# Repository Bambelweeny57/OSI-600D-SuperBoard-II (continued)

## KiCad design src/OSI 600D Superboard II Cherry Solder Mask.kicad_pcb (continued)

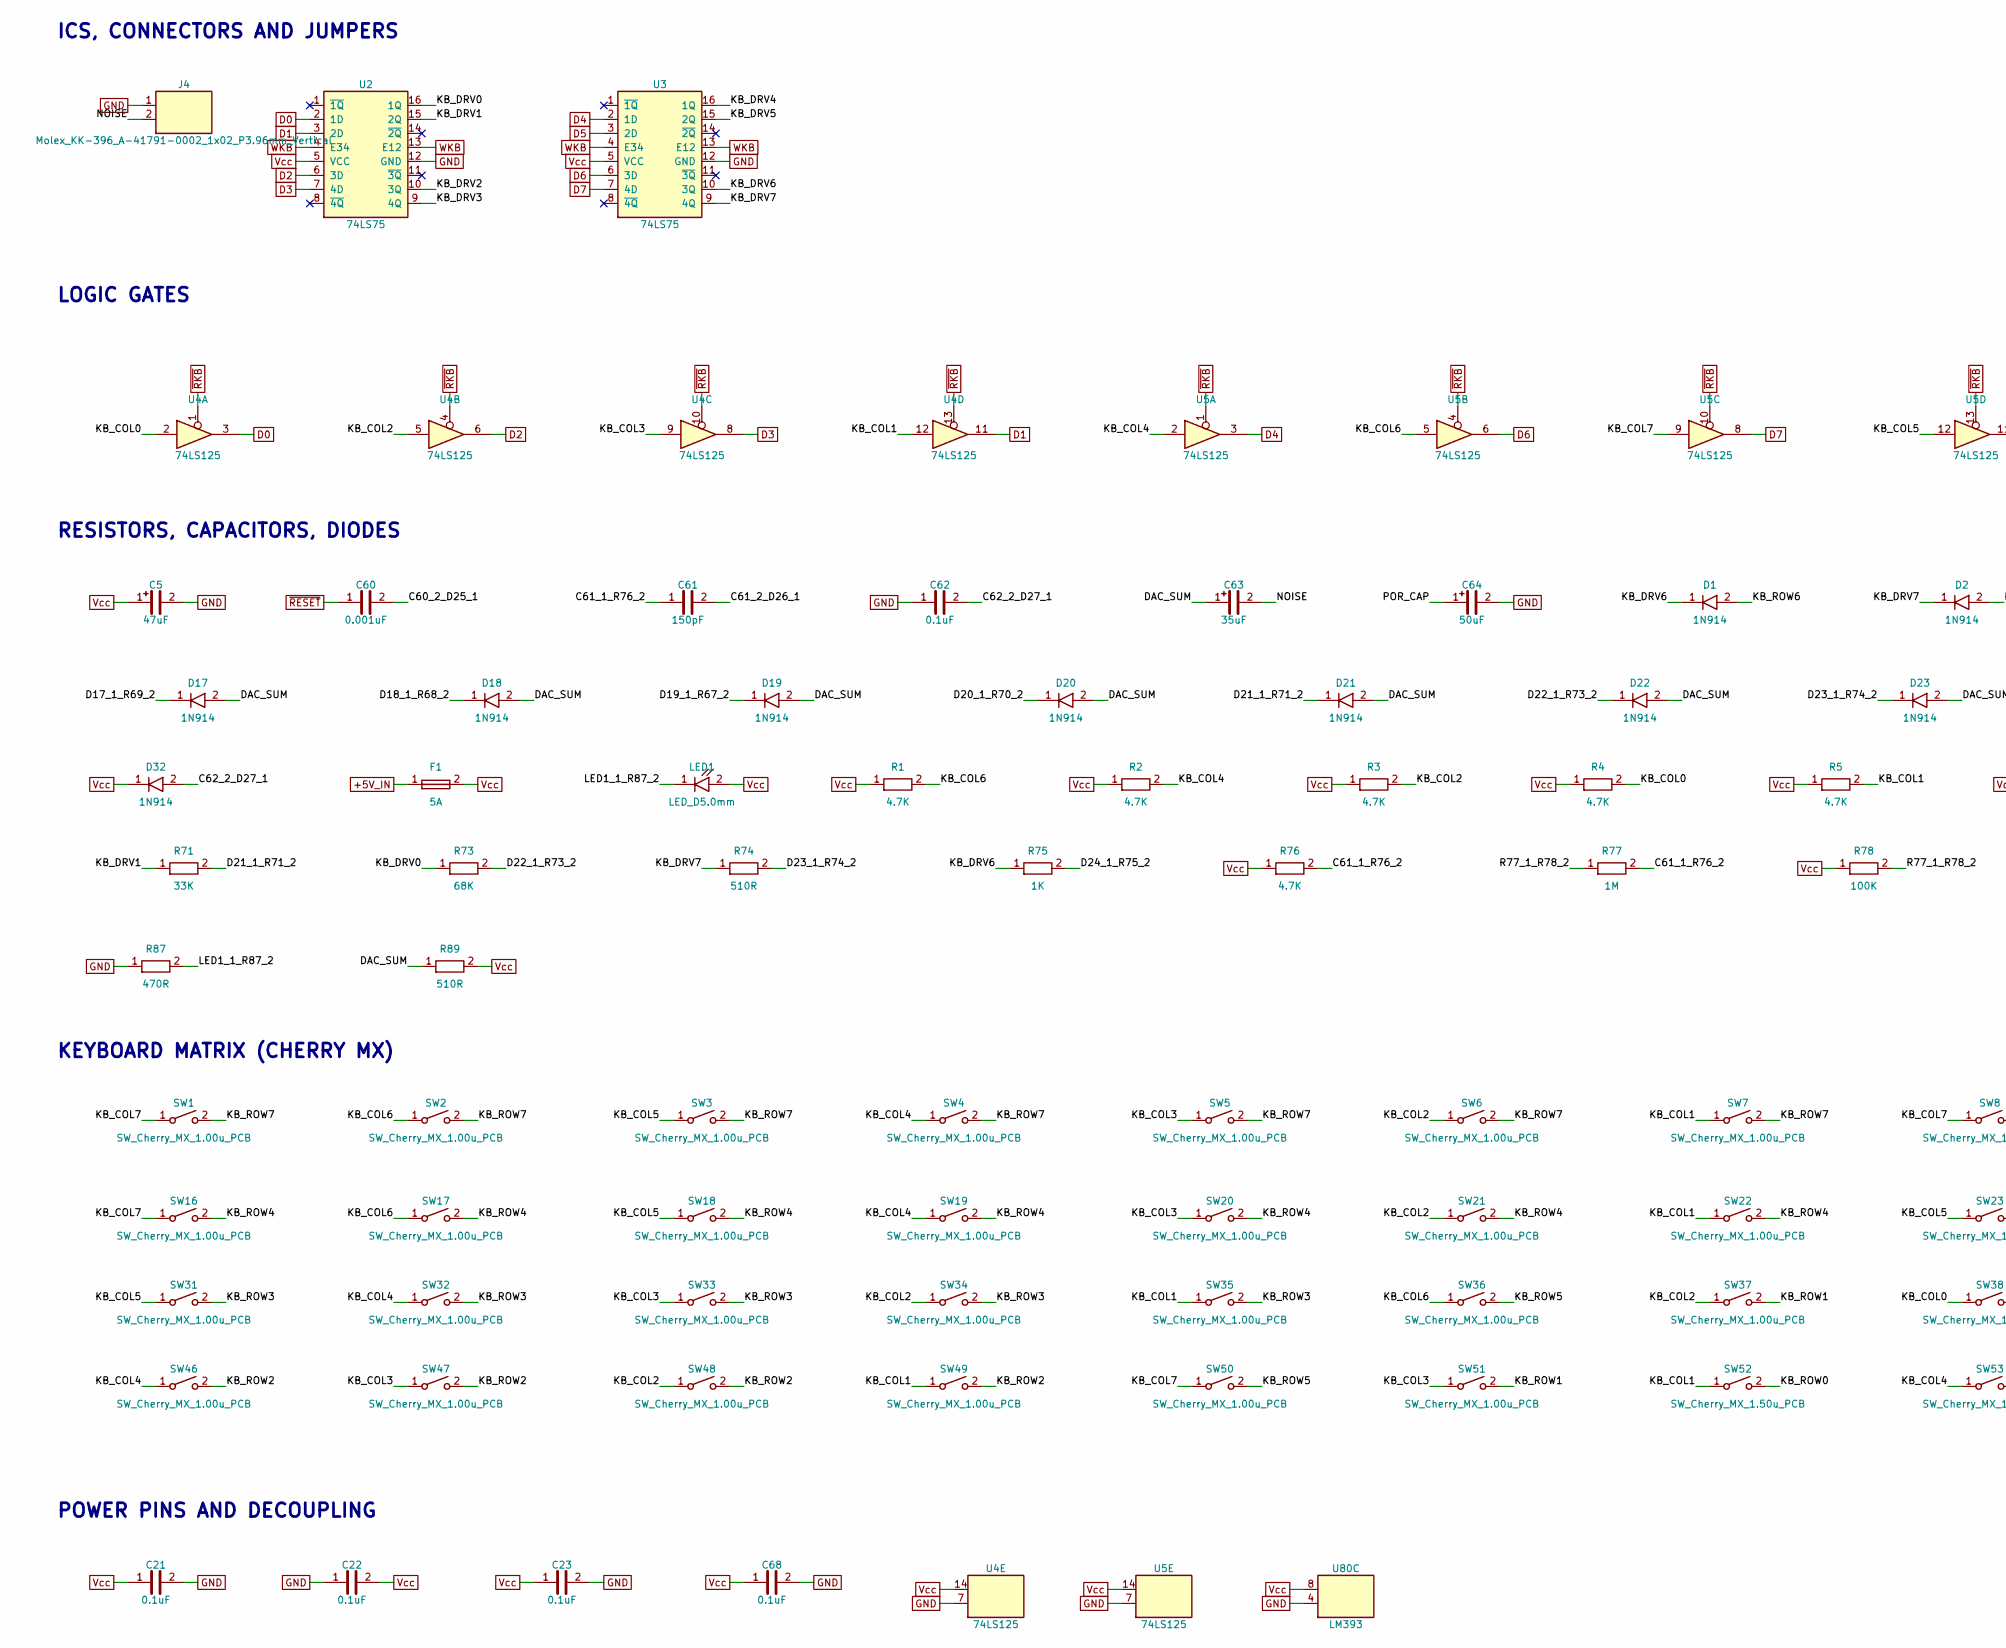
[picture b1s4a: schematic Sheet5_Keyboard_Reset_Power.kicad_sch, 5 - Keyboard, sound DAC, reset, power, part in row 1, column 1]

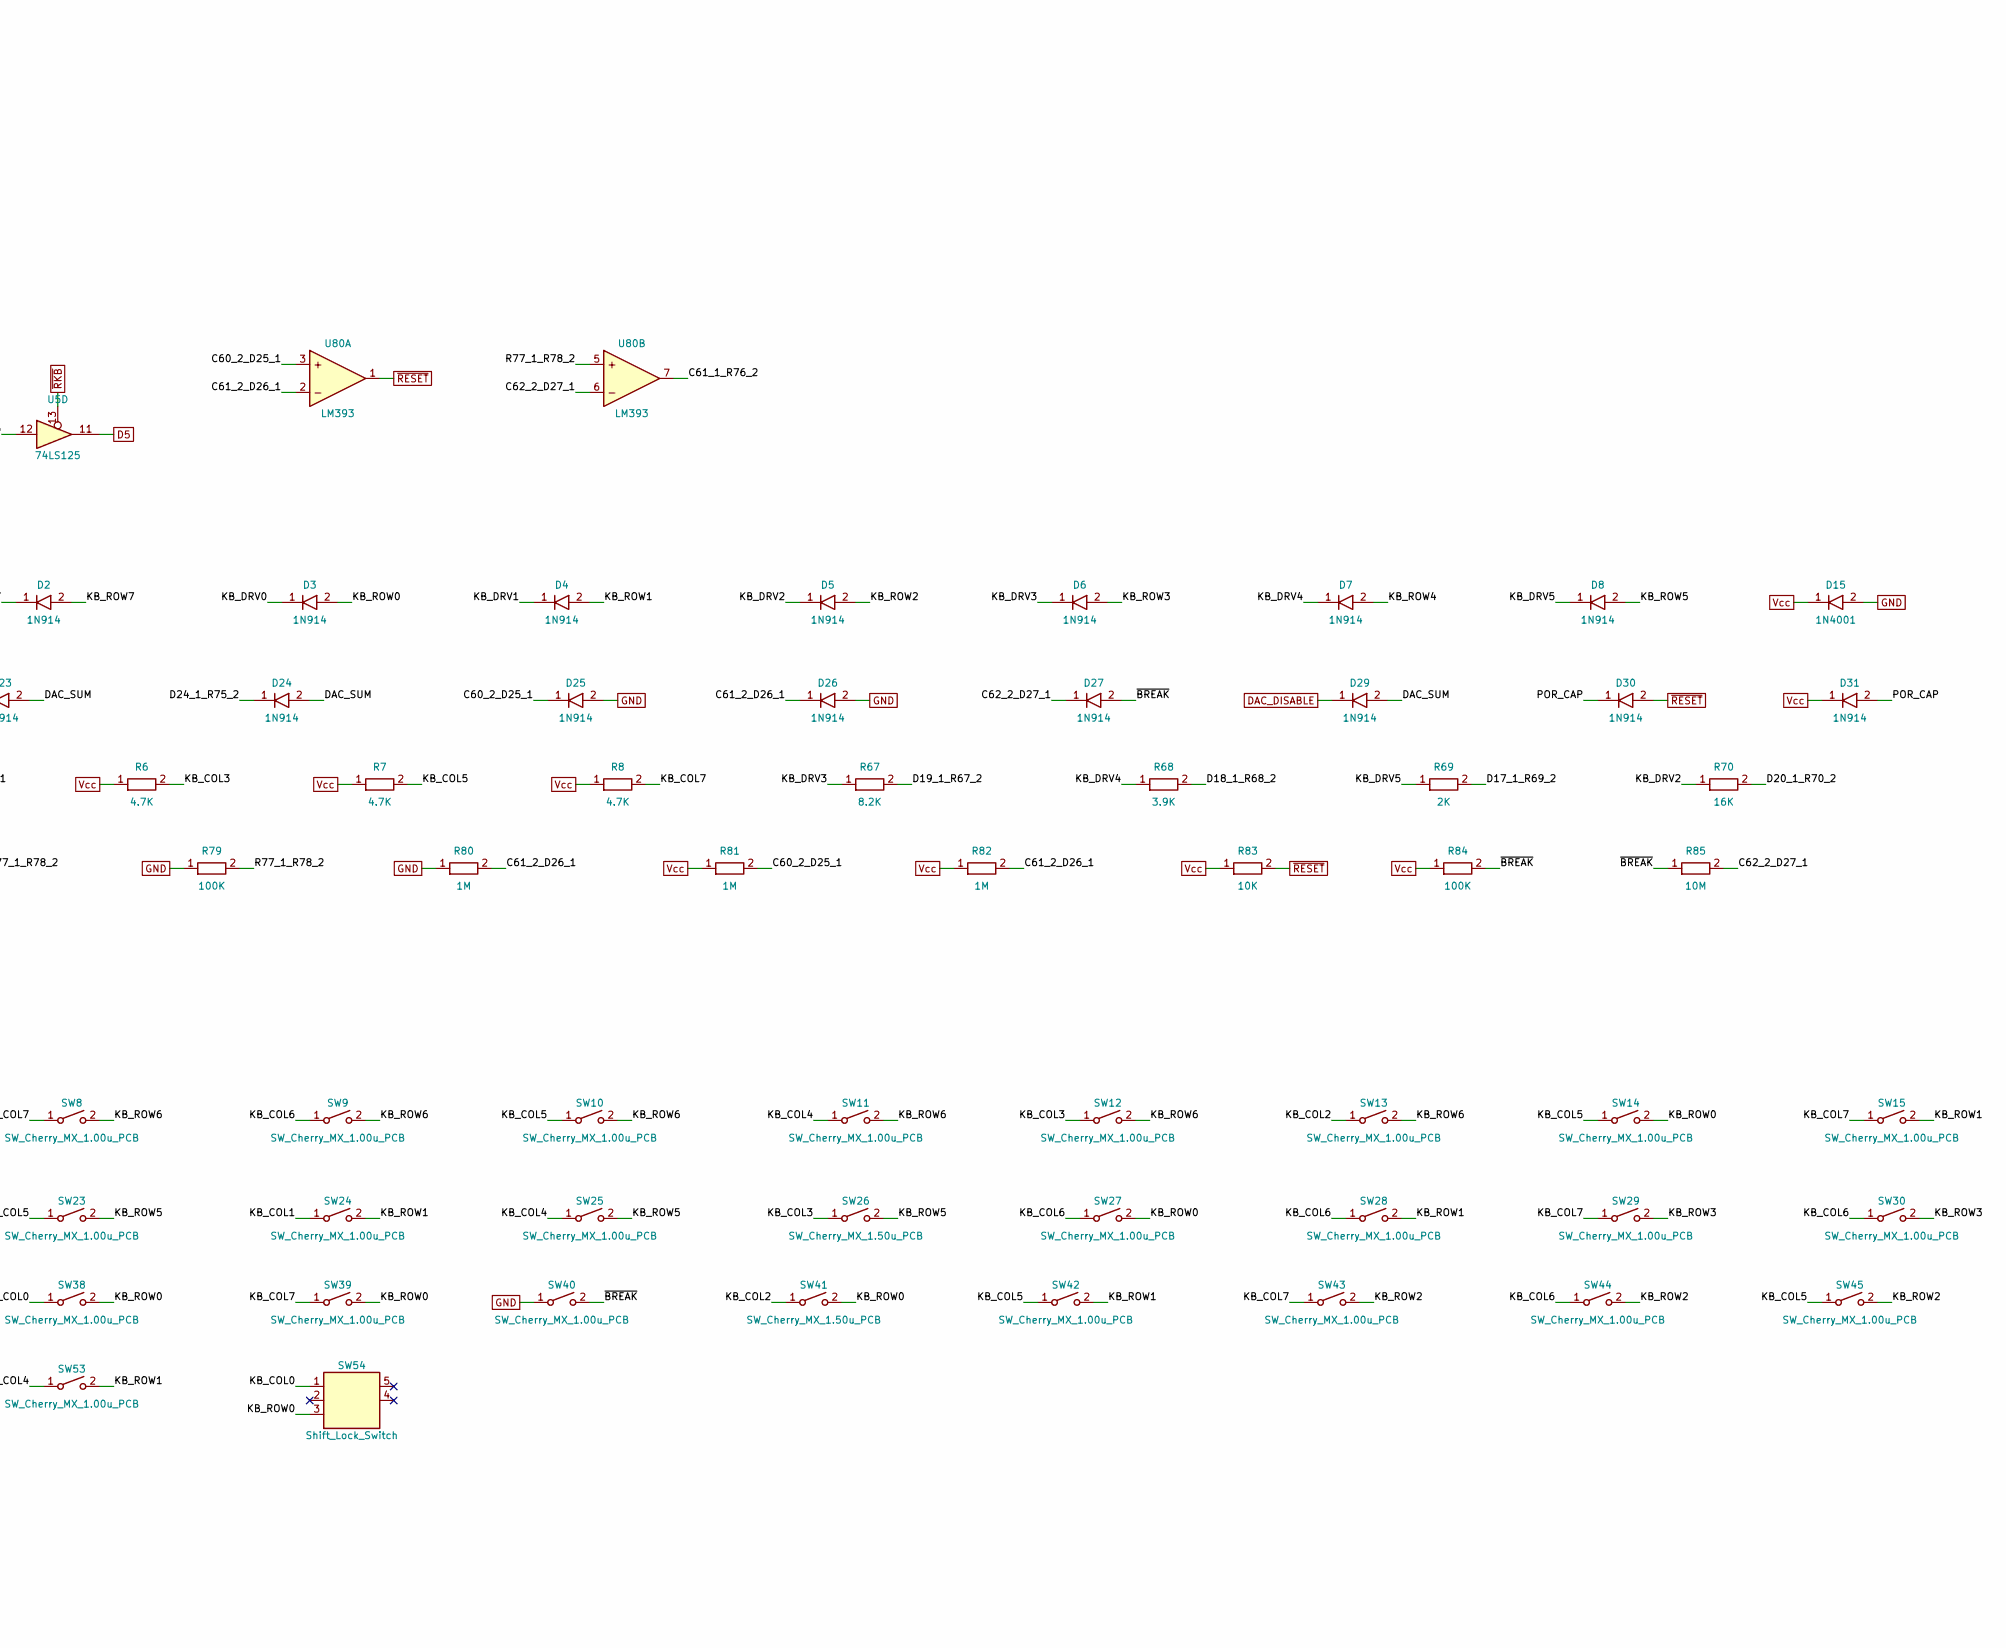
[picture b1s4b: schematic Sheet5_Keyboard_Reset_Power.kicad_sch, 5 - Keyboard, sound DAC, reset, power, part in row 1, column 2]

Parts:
C5: 47uF; CP_Axial_L10.0mm_D4.5mm_P15.00mm_Horizontal
C21, C22, C23, C62, C68: 0.1uF; C_Rect_L10.0mm_W3.0mm_P7.50mm_FKS3_FKP3
C60: 0.001uF; C_Rect_L10.0mm_W3.0mm_P7.50mm_FKS3_FKP3
C61: 150pF; C_Rect_L10.0mm_W3.0mm_P7.50mm_FKS3_FKP3
C63: 35uF; CP_Axial_L11.0mm_D6.0mm_P20.32mm_Horizontal
C64: 50uF; CP_Axial_L11.0mm_D6.0mm_P20.32mm_Horizontal
D1, D2, D3, D4, D5, D6, D7, D8, D17, D18, D19, D20, D21, D22, D23, D24, D25, D26, D27, D29, D30, D31, D32: 1N914; D_DO-34_SOD68_P10.16mm_Horizontal
D15: 1N4001; D_DO-35_SOD27_P12.70mm_Horizontal
F1: 5A; Fuseholder_Clip-6.3x32mm_Littelfuse_102_Inline_P34.21x7.62m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
J4: Molex_KK-396_A-41791-0002_1x02_P3.96mm_Vertical
LED1: LED_D5.0mm
R1, R2, R3, R4, R5, R6, R7, R8: 4.7K; R_Axial_DIN0207_L6.3mm_D2.5mm_P2.54mm_Vertical
R67: 8.2K; R_Axial_DIN0207_L6.3mm_D2.5mm_P2.54mm_Vertical
R68: 3.9K; R_Axial_DIN0207_L6.3mm_D2.5mm_P2.54mm_Vertical
R69: 2K; R_Axial_DIN0207_L6.3mm_D2.5mm_P2.54mm_Vertical
R70: 16K; R_Axial_DIN0207_L6.3mm_D2.5mm_P2.54mm_Vertical
R71: 33K; R_Axial_DIN0207_L6.3mm_D2.5mm_P2.54mm_Vertical
R73: 68K; R_Axial_DIN0207_L6.3mm_D2.5mm_P2.54mm_Vertical
R74: 510R; R_Axial_DIN0207_L6.3mm_D2.5mm_P2.54mm_Vertical
R75: 1K; R_Axial_DIN0207_L6.3mm_D2.5mm_P2.54mm_Vertical
R76: 4.7K; R_Yageo_L3.6mm_D1.6mm_P12.70mm_Horizontal
R77, R80, R81, R82: 1M; R_Yageo_L3.6mm_D1.6mm_P12.70mm_Horizontal
R78, R79, R84: 100K; R_Yageo_L3.6mm_D1.6mm_P12.70mm_Horizontal
R83: 10K; R_Yageo_L3.6mm_D1.6mm_P12.70mm_Horizontal
R85: 10M; R_Yageo_L3.6mm_D1.6mm_P12.70mm_Horizontal
R87: 470R; R_Axial_DIN0207_L6.3mm_D2.5mm_P2.54mm_Vertical
R89: 510R; R_Yageo_L3.6mm_D1.6mm_P12.70mm_Horizontal
SW1, SW2, SW3, SW4, SW5, SW6, SW7, SW8, SW9, SW10, SW11, SW12, SW13, SW14, SW15, SW16, SW17, SW18, SW19, SW20, SW21, SW22, SW23, SW24, SW25, SW27, SW28, SW29, SW30, SW31, SW32, SW33, SW34, SW35, SW36, SW37, SW38, SW39, SW40, SW42, SW43, SW44, SW45, SW46, SW47, SW48, SW49, SW50, SW51, SW53: SW_Cherry_MX_1.00u_PCB
SW26, SW41, SW52: SW_Cherry_MX_1.50u_PCB
SW54: Shift_Lock_Switch
U2, U3: 74LS75; DIP-16_W7.62mm_LongPads
U4, U5: 74LS125; DIP-14_W7.62mm_LongPads
U80: LM393; DIP-8_W7.62mm_LongPads

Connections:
+5V_IN: F1.1
C60_2_D25_1: C60.2, D25.1, R81.2, U80.3
C61_1_R76_2: C61.1, R76.2, R77.2, U80.7
C61_2_D26_1: C61.2, D26.1, R80.2, R82.2, U80.2
C62_2_D27_1: C62.2, D27.1, D32.2, R85.2, U80.6
D0: U2.2 (1D), U4.3; also elsewhere on the board
D1: U2.3 (2D), U4.11; also elsewhere on the board
D2: U2.6 (3D), U4.6; also elsewhere on the board
D3: U2.7 (4D), U4.8; also elsewhere on the board
D4: U3.2 (1D), U5.3; also elsewhere on the board
D5: U3.3 (2D), U5.11; also elsewhere on the board
D6: U3.6 (3D), U5.6; also elsewhere on the board
D7: U3.7 (4D), U5.8; also elsewhere on the board
D17_1_R69_2: D17.1, R69.2
D18_1_R68_2: D18.1, R68.2
D19_1_R67_2: D19.1, R67.2
D20_1_R70_2: D20.1, R70.2
D21_1_R71_2: D21.1, R71.2
D22_1_R73_2: D22.1, R73.2
D23_1_R74_2: D23.1, R74.2
D24_1_R75_2: D24.1, R75.2
DAC_DISABLE: D29.1; also elsewhere on the board
DAC_SUM: C63.1, D17.2, D18.2, D19.2, D20.2, D21.2, D22.2, D23.2, D24.2, D29.2, R89.1
GND: C5.2, C21.2, C22.1, C23.2, C62.1, C64.2, C68.2, D15.2, D25.2, D26.2, J4.1, R79.1, R80.1, R87.1, SW40.1, U2.12 (GND), U3.12 (GND), U4.7 (GND), U5.7 (GND), U80.4 (GND); also elsewhere on the board
KB_COL0: R4.2, SW38.1, SW54.1, U4.2
KB_COL1: R5.2, SW7.1, SW22.1, SW24.1, SW35.1, SW49.1, SW52.1, U4.12
KB_COL2: R3.2, SW6.1, SW13.1, SW21.1, SW34.1, SW37.1, SW41.1, SW48.1, U4.5
KB_COL3: R6.2, SW5.1, SW12.1, SW20.1, SW26.1, SW33.1, SW47.1, SW51.1, U4.9
KB_COL4: R2.2, SW4.1, SW11.1, SW19.1, SW25.1, SW32.1, SW46.1, SW53.1, U5.2
KB_COL5: R7.2, SW3.1, SW10.1, SW14.1, SW18.1, SW23.1, SW31.1, SW42.1, SW45.1, U5.12
KB_COL6: R1.2, SW2.1, SW9.1, SW17.1, SW27.1, SW28.1, SW30.1, SW36.1, SW44.1, U5.5
KB_COL7: R8.2, SW1.1, SW8.1, SW15.1, SW16.1, SW29.1, SW39.1, SW43.1, SW50.1, U5.9
KB_DRV0: D3.1, R73.1, U2.16 (1Q)
KB_DRV1: D4.1, R71.1, U2.15 (2Q)
KB_DRV2: D5.1, R70.1, U2.10 (3Q)
KB_DRV3: D6.1, R67.1, U2.9 (4Q)
KB_DRV4: D7.1, R68.1, U3.16 (1Q)
KB_DRV5: D8.1, R69.1, U3.15 (2Q)
KB_DRV6: D1.1, R75.1, U3.10 (3Q)
KB_DRV7: D2.1, R74.1, U3.9 (4Q)
KB_ROW0: D3.2, SW14.2, SW27.2, SW38.2, SW39.2, SW41.2, SW52.2, SW54.3
KB_ROW1: D4.2, SW15.2, SW24.2, SW28.2, SW37.2, SW42.2, SW51.2, SW53.2
KB_ROW2: D5.2, SW43.2, SW44.2, SW45.2, SW46.2, SW47.2, SW48.2, SW49.2
KB_ROW3: D6.2, SW29.2, SW30.2, SW31.2, SW32.2, SW33.2, SW34.2, SW35.2
KB_ROW4: D7.2, SW16.2, SW17.2, SW18.2, SW19.2, SW20.2, SW21.2, SW22.2
KB_ROW5: D8.2, SW23.2, SW25.2, SW26.2, SW36.2, SW50.2
KB_ROW6: D1.2, SW8.2, SW9.2, SW10.2, SW11.2, SW12.2, SW13.2
KB_ROW7: D2.2, SW1.2, SW2.2, SW3.2, SW4.2, SW5.2, SW6.2, SW7.2
LED1_1_R87_2: LED1.1, R87.2
NOISE: C63.2, J4.2
POR_CAP: C64.1, D30.1, D31.2
R77_1_R78_2: R77.1, R78.2, R79.2, U80.5
Vcc: C5.1, C21.1, C22.2, C23.1, C68.1, D15.1, D31.1, D32.1, F1.2, LED1.2, R1.1, R2.1, R3.1, R4.1, R5.1, R6.1, R7.1, R8.1, R76.1, R78.1, R81.1, R82.1, R83.1, R84.1, R89.2, U2.5 (VCC), U3.5 (VCC), U4.14 (VCC), U5.14 (VCC), U80.8 (VCC); also elsewhere on the board
WKB: U2.4 (E34), U2.13 (E12), U3.4 (E34), U3.13 (E12); also elsewhere on the board
~BREAK: D27.2, R84.2, R85.1, SW40.2
~RESET: C60.1, D30.2, R83.2, U80.1; also elsewhere on the board
~RKB: U4.1, U4.4, U4.10, U4.13, U5.1, U5.4, U5.10, U5.13; also elsewhere on the board

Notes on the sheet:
ICS, CONNECTORS AND JUMPERS
LOGIC GATES
RESISTORS, CAPACITORS, DIODES
KEYBOARD MATRIX (CHERRY MX)
POWER PINS AND DECOUPLING

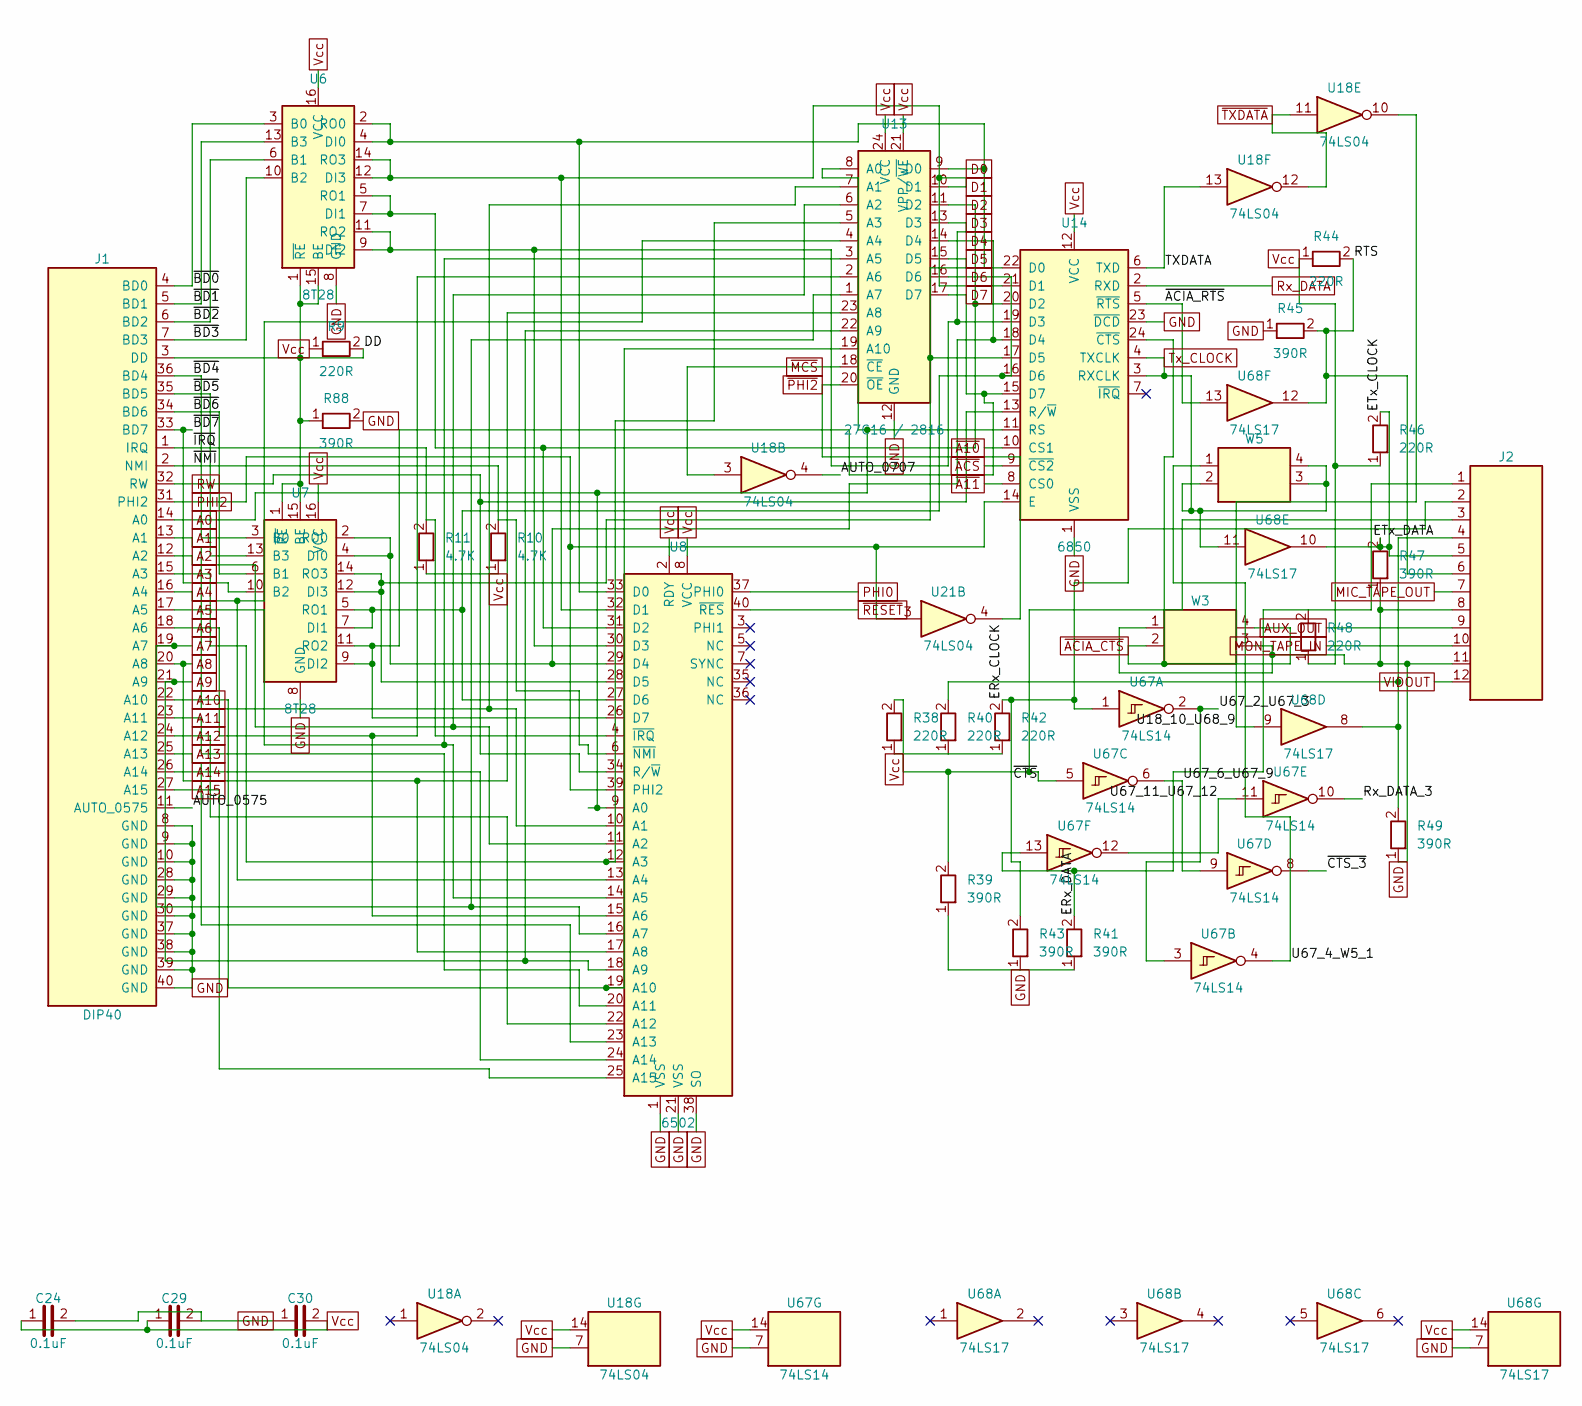
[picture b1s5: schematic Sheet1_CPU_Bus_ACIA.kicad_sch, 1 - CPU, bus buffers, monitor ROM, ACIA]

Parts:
C24, C29, C30: 0.1uF; C_Rect_L10.0mm_W3.0mm_P7.50mm_FKS3_FKP3
J1: DIP40; DIP-40_W15.24mm_LongPads
J2: CONN_SDA-41815_12_RA_MOL
R9, R38, R40, R42, R44, R46, R48: 220R; R_Axial_DIN0207_L6.3mm_D2.5mm_P2.54mm_Vertical
R10, R11: 4.7K; R_Axial_DIN0207_L6.3mm_D2.5mm_P2.54mm_Vertical
R39, R41, R43, R45, R47, R49, R88: 390R; R_Axial_DIN0207_L6.3mm_D2.5mm_P2.54mm_Vertical
U6, U7: 8T28; DIP-16_W7.62mm_LongPads
U8: 6502; DIP-40_W15.24mm_LongPads
U13: 27C16 / 2816; DIP-24_W15.24mm_LongPads
U14: 6850; DIP-24_W15.24mm_LongPads
U18, U21: 74LS04; DIP-14_W7.62mm_LongPads
U67: 74LS14; DIP-14_W7.62mm_LongPads
U68: 74LS17; DIP-14_W7.62mm_LongPads
W3, W5: PinHeader_2x02_P2.54mm_Vertical

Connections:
A0: J1.14 (A0), U8.9 (A0), U13.8 (A0), U14.11 (RS); also elsewhere on the board
A1: J1.13 (A1), U8.10 (A1), U13.7 (A1); also elsewhere on the board
A2: J1.12 (A2), U8.11 (A2), U13.6 (A2); also elsewhere on the board
A3: J1.15 (A3), U8.12 (A3), U13.5 (A3); also elsewhere on the board
A4: J1.16 (A4), U8.13 (A4), U13.4 (A4); also elsewhere on the board
A5: J1.17 (A5), U8.14 (A5), U13.3 (A5); also elsewhere on the board
A6: J1.18 (A6), U8.15 (A6), U13.2 (A6); also elsewhere on the board
A7: J1.19 (A7), U8.16 (A7), U13.1 (A7); also elsewhere on the board
A8: J1.20 (A8), U8.17 (A8), U13.23 (A8); also elsewhere on the board
A9: J1.21 (A9), U8.18 (A9), U13.22 (A9); also elsewhere on the board
A10: J1.22 (A10), U8.19 (A10), U13.19 (A10); also elsewhere on the board
A11: J1.23 (A11), U8.20 (A11); also elsewhere on the board
A12: J1.24 (A12), U8.22 (A12); also elsewhere on the board
A13: J1.25 (A13), U8.23 (A13); also elsewhere on the board
A14: J1.26 (A14), U8.24 (A14); also elsewhere on the board
A15: J1.27 (A15), U8.25 (A15); also elsewhere on the board
AUTO_0575: J1.11 (AUTO_0575)
AUTO_0707: U18.4
AUX_OUT: J2.9; also elsewhere on the board
D0: U6.2 (RO0), U6.4 (DI0), U8.33 (D0), U13.9 (D0), U14.22 (D0); also elsewhere on the board
D1: U6.12 (DI3), U6.14 (RO3), U8.32 (D1), U13.10 (D1), U14.21 (D1); also elsewhere on the board
D2: U6.5 (RO1), U6.7 (DI1), U8.31 (D2), U13.11 (D2), U14.20 (D2); also elsewhere on the board
D3: U6.9 (DI2), U6.11 (RO2), U8.30 (D3), U13.13 (D3), U14.19 (D3); also elsewhere on the board
D4: U7.2 (RO0), U7.4 (DI0), U8.29 (D4), U13.14 (D4), U14.18 (D4); also elsewhere on the board
D5: U7.12 (DI3), U7.14 (RO3), U8.28 (D5), U13.15 (D5), U14.17 (D5); also elsewhere on the board
D6: U7.5 (RO1), U7.7 (DI1), U8.27 (D6), U13.16 (D6), U14.16 (D6); also elsewhere on the board
D7: U7.9 (DI2), U7.11 (RO2), U8.26 (D7), U13.17 (D7), U14.15 (D7); also elsewhere on the board
DD: J1.3 (DD), R9.2, R88.1, U6.1 (~RE), U6.15 (BE), U7.1 (~RE), U7.15 (BE)
ERx_CLOCK: J2.2, R42.2, R43.2, U67.1
ERx_DATA: J2.1, R41.2, R48.2, U67.13
ETx_CLOCK: J2.5, R46.2, R47.2, U68.10
ETx_DATA: J2.4, R40.2, R49.2, U68.8
GND: C24.2, C29.2, C30.1, J1.8 (GND), J1.9 (GND), J1.10 (GND), J1.28 (GND), J1.29 (GND), J1.30 (GND), J1.37 (GND), J1.38 (GND), J1.39 (GND), J1.40 (GND), J2.8, J2.11, R39.1, R41.1, R43.1, R45.1, R47.1, R49.1, R88.2, U6.8 (GND), U7.8 (GND), U8.1 (VSS), U8.21 (VSS), U8.38 (SO), U13.12 (GND), U14.1 (VSS), U14.23 (~DCD), U18.7 (GND), U67.7 (GND), U68.7 (GND), W3.1, W3.3; also elsewhere on the board
MIC_TAPE_OUT: J2.7; also elsewhere on the board
MON_TAPE_IN: J2.10; also elsewhere on the board
PHI0: U8.37 (PHI0); also elsewhere on the board
PHI2: J1.31 (PHI2), U8.39 (PHI2), U14.14 (E), U21.3; also elsewhere on the board
RTS: J2.6, R44.2, R45.2, U68.12
RW: J1.32 (RW), U8.34 (R/~W), U14.13 (R/~W); also elsewhere on the board
Rx_DATA: U14.2 (RXD); also elsewhere on the board
Rx_DATA_3: U67.10
TXDATA: U14.6 (TXD), U18.13
Tx_CLOCK: U14.3 (RXCLK), U14.4 (TXCLK), U68.11, W5.2, W5.3, W5.4; also elsewhere on the board
U18_10_U68_9: U18.10, U68.9
U67_2_U67_3: U67.2, U67.3
U67_4_W5_1: U67.4, W5.1
U67_6_U67_9: U67.6, U67.9
U67_11_U67_12: U67.11, U67.12
VIDOUT: J2.12; also elsewhere on the board
Vcc: C24.1, C29.1, C30.2, R9.1, R10.1, R11.1, R38.1, R40.1, R42.1, R44.1, R46.1, R48.1, U6.16 (VCC), U7.16 (VCC), U8.2 (RDY), U8.8 (VCC), U13.21 (VPP/~WE), U13.24 (VCC), U14.12 (VCC), U18.14 (VCC), U67.14 (VCC), U68.14 (VCC); also elsewhere on the board
~A10: U14.10 (CS1); also elsewhere on the board
~A11: U14.8 (CS0); also elsewhere on the board
~ACIA_CTS: U14.24 (~CTS), W3.2, W3.4; also elsewhere on the board
~ACIA_RTS: U14.5 (~RTS), U68.13
~ACS: U14.9 (~CS2); also elsewhere on the board
~BD0: J1.4 (BD0), U6.3 (B0)
~BD1: J1.5 (BD1), U6.13 (B3)
~BD2: J1.6 (BD2), U6.6 (B1)
~BD3: J1.7 (BD3), U6.10 (B2)
~BD4: J1.36 (BD4), U7.3 (B0)
~BD5: J1.35 (BD5), U7.13 (B3)
~BD6: J1.34 (BD6), U7.6 (B1)
~BD7: J1.33 (BD7), U7.10 (B2)
~CTS_3: U67.8
~CTS: J2.3, R38.2, R39.2, U67.5
~IRQ: J1.1 (IRQ), R11.2, U8.4 (~IRQ)
~MCS: U13.18 (~CE), U18.3; also elsewhere on the board
~NMI: J1.2 (NMI), R10.2, U8.6 (~NMI)
~PHI2: U13.20 (~OE), U21.4; also elsewhere on the board
~RESET: U8.40 (~RES); also elsewhere on the board
~TXDATA: U18.11, U18.12; also elsewhere on the board
